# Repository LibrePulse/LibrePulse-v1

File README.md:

# PROJECT CURRENTLY IN THE MIDDLE OF SIGNIFICANT REDESIGN FROM THE INITIAL DRAFT

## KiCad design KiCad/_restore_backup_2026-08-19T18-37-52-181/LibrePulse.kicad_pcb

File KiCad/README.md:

# TODO:
## Cleanup
## Finish Schematic
## Start PCB

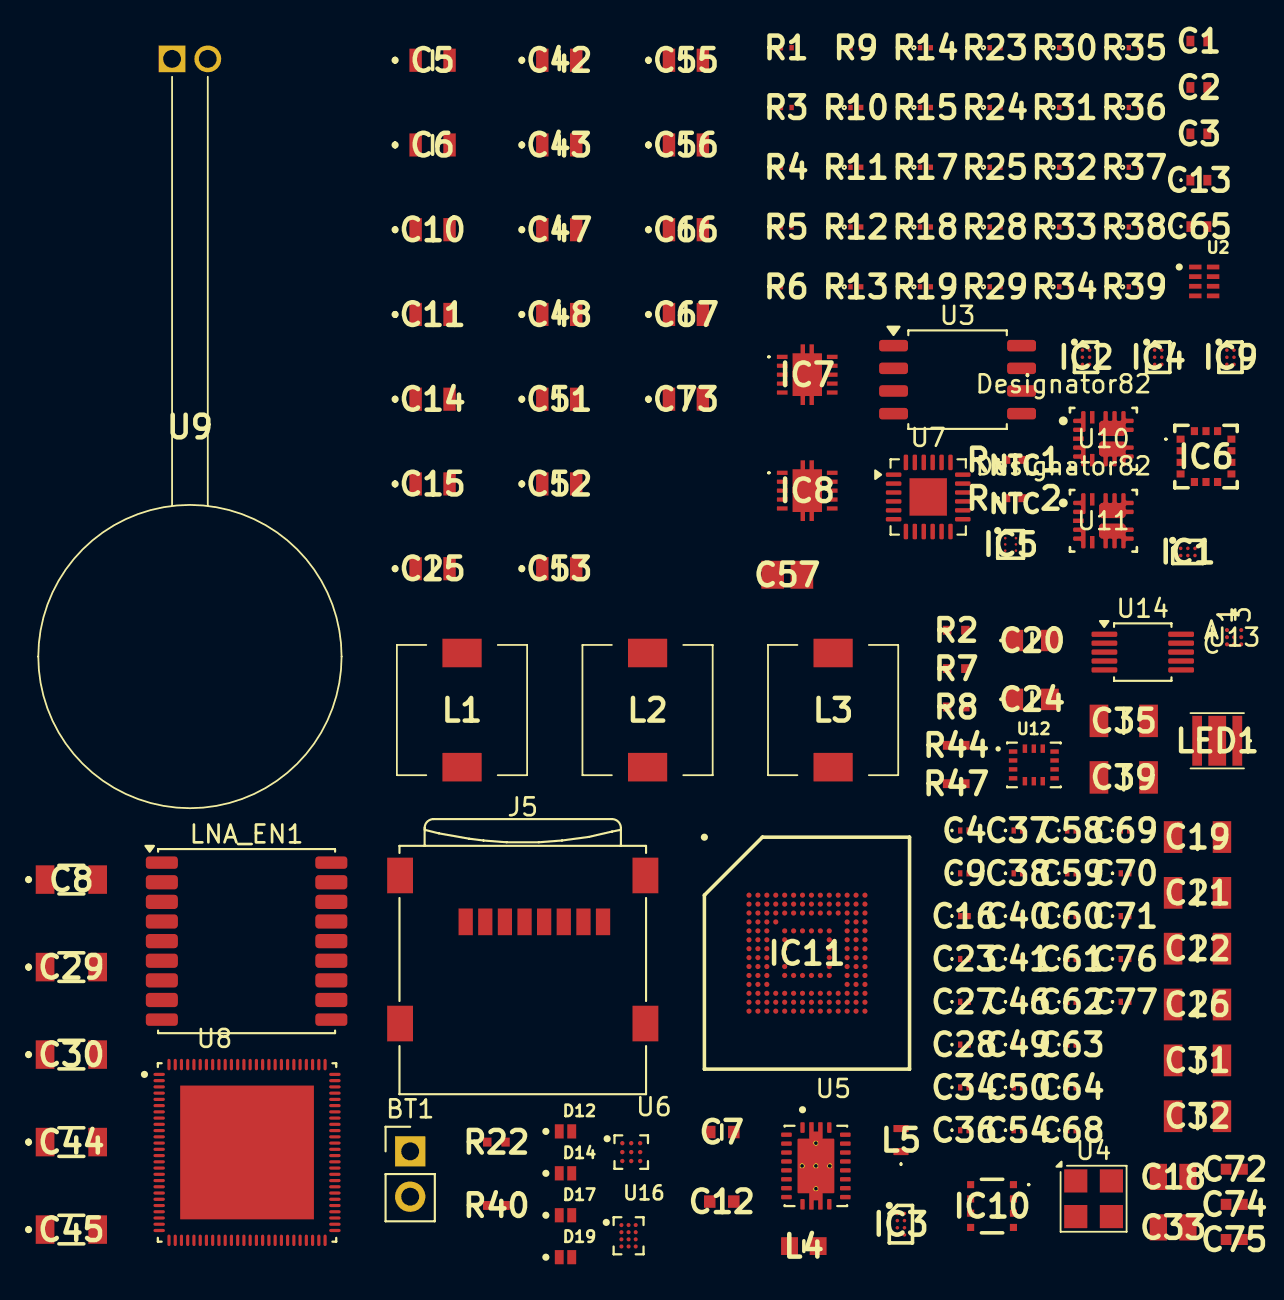
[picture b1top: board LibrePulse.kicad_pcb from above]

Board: 8 copper layers, 153 parts (0 on the bottom side), 104 nets, no tracks yet.

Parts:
BT1: DTP793435-1S1P-1300mAh-3.85V; PinHeader_1x02_P2.54mm_Vertical
C1, C2, C3, C13, C65: 1uF; GRM155R61H334ME01D
C4, C9, C16, C27, C28, C34, C36, C37, C38, C40, C41, C46, C49, C50, C54, C58, C59, C61, C62, C63, C64, C68, C69, C70, C71, C76, C77: 100nF; GRM033D70J224ME01D
C5, C10, C11, C15, C25, C42, C43, C47, C48, C51, C52, C55, C56, C66, C67, C73: 10uF; GRM21BR60J226ME39L
C6, C14, C53: 4.7uF; GRM21BR60J226ME39L
C7, C12: 2.2uF; GRM18x
C8, C29, C30, C44, C45: 22uF; GRM31x
C18, C33: 22nF; CAPC2012X145N
C19, C26: 10nF; CAPC3216X95N
C20, C24: 100nF; GRMJN65C1H104JE01D
C21, C22, C31, C32: 47nF; CAPC3216X95N
C23: 1nF; GRM033D70J224ME01D
C35, C39: 470nF; CAPC3216X180N
C57: 2.2uF; CAPC2212X200N
C60: 47pF; GRM033D70J224ME01D
C72, C74, C75: 47pF; CAPC1005X55N
D12, D14, D17, D19: PESD5V0V1BL; DIO_PESD5V5C1ULYL
IC1: AS6221; BGA6C40P3X2_149X102X60
IC2: TPS62841YBGR; BGA6C40P2X3_97X147X50
IC3: BQ21088YBGR; BGA8C40P2X4_100X155X50
IC4, IC9: TPS62840YBGR; BGA6C40P2X3_97X147X50
IC5: OPT3007YMFR; BGA6C35P2X3_86X95X23
IC6: ICU-10201; ICU10201
IC7, IC8: TPS7A9601DSCR
IC10: BME690
IC11: KLMCG4JETD-B041; BGA153C50P14X14_1150X1300X80
J5: Micro_SD_Card; microSD_HC_Wuerth_693072010801
L1, L2, L3: 2.2uH; 744777002
L4: 1uH; INDC1608X80N
L5: 0603DC-47NXJRW; 0603DC47NXJRW
LED1: KW_CSLPM1.TG-8N7P-EBVF46FCBB46; KWCSLNM1TG8M7NebvF46fcbB4615B5
LNA_EN1: MAX-M10S; ublox_MAX
R1, R3, R5, R6: 10K; ERJU01__0201_
R2, R7, R8: 47k; ERJ2RKD1004X
R4: 16k; ERJU01__0201_
R9, R10: 33; ERJU01__0201_
R11, R18, R19: 1M; ERJU01__0201_
R12, R17: 51k; ERJU01__0201_
R13: 196; ERJU01__0201_
R14: 10kΩ; ERJU01__0201_
R15, R33, R34: 10k; ERJU01__0201_
R22, R40: 10k; ERJS02_U02__0402_
R23, R24, R28, R29: 5.1k; ERJU01__0201_
R25: 1.5k; ERJU01__0201_
R30: 7.87k; ERJU01__0201_
R31: 11.5k; ERJU01__0201_
R32, R35: 30k; ERJU01__0201_
R36, R38: 12.7k; ERJU01__0201_
R37: 240k; ERJU01__0201_
R39: 90.9k; ERJU01__0201_
R44, R47: 4.7k; ERJ2RKD1004X
R_{NTC}1, R_{NTC}2: 10K; ERTJ0EA101H
U2: RV-3028-C8-32.768KHZ-1PPM-TA-QC
U3: W25Q128JVS; SOIC-8_5.3x5.3mm_P1.27mm
U4: MS5837-30BA; TE_MS5837-xxBA
U5: BQ51013CQWRHLRQ1; IC_BQ51013CQWRHLRQ1
U6: BQ27427YZFR
U7: PCAL6416AHF; HVQFN-24-1EP_4x4mm_P0.5mm_EP2.1x2.1mm
U8: ESP32-P4NRW32
U9: 760308101214
U10, U11: TPSM81299VCMR; VCM0007A-MFG
U12: BMI270
U13: BMM350
U14: DRV2605LDGS; TSSOP-10_3x3mm_P0.5mm
U16: LM3643YFFR; IC_LM3643YFFR

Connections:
+1V2: C5.1, C49.1, C55.1, IC2.A2 (VOS), L1.2, U8.26 (VDD_HP_0), U8.76 (VDD_HP_2), U8.91 (VDD_HP_3)
+1V8: C1.2, C2.2, C3.1, C34.1, C37.1, C45.1, C52.1, IC6.12 (VDD), IC6.13 (AVDD), IC8.8 (SNS), IC8.9 (OUT_1), IC8.10 (OUT_2), R39.2
+1V9: C11.1, C41.1, C43.1, C48.2, IC4.A2 (VOS), IC8.1 (IN_1), IC8.2 (IN_2), L2.2, R34.2, U8.9 (VDD_LP), U8.30 (VDD_FLASHIO), U8.59 (VDD_PSRAM_0), U8.67 (VDD_PSRAM_1), U8.71 (VDDO_FLASH), U8.72 (VDDO_PSRAM), U8.73 (VDDO_3), U8.74 (VDDO_4)
+2V5: C40.1, C42.1, C51.1, IC9.A2 (VOS), L3.2, U8.41 (VDD_MIPI_DPHY)
+3V3: C4.1, C27.1, C28.1, C30.1, C36.1, C38.1, C46.2, C50.1, C54.2, C56.1, C58.2, C59.1, C62.2, C63.2, C64.1, C66.1, C68.2, C69.2, C70.1, C71.2, C77.1, IC1.B1 (VDD), IC5.C1 (VDD), IC6.14 (VDDIO), IC10.2 (CSB), IC10.6 (VDDIO), IC10.8 (VDD), IC11.C6 (VDD_1), IC11.E6 (VDDF_1), IC11.F5 (VDDF_2), IC11.J10 (VDDF_3), IC11.K9 (VDDF_4), IC11.M4 (VDD_2), IC11.N4 (VDD_3), IC11.P3 (VDD_4), IC11.P5 (VDD_5), J5.4 (VDD), L4.2, LNA_EN1.6 (V_BCKP), LNA_EN1.7 (VCC_IO), LNA_EN1.8 (VCC), R1.2, R2.2, R3.2, R5.2, R14.2, R22.2, R44.2, R47.2, U2.7 (VDD), U3.8 (VCC), U4.2 (VDD), U7.21 (V_{DD(P)}), U7.23 (V_{DD(I2C-bus)}), U8.21 (VDD_IO_0), U8.51 (VDD_USBPHY), U8.62 (VDD_IO_4), U8.75 (VDD_LDO), U8.77 (VDD_DCDCC), U8.85 (VDD_IO_5), U8.96 (VDD_IO_6), U8.101 (VDD_ANA), U8.102 (VDD_BAT), U11.2 (VOUT), U12.2 (ASDX), U12.3 (ASCX), U12.5 (VDDIO), U12.8 (VDD), U12.12 (CSB), U13.B3 (VDDIO), U13.C1 (VDD), U14.6 (VDD/NC), U14.10 (VDD), U16.A2 (IN)
+4V5: C44.1, IC7.9 (OUT_1), IC7.10 (OUT_2), R37.2
+5V0: C29.1, C47.2, IC7.1 (IN_1), IC7.2 (IN_2), R33.2, U10.2 (VOUT)
+VSYS: BT1.1 (+), C8.1, C12.2, C13.1, IC3.B2 (SYS), IC3.C2 (BAT), R15.2, R18.2, R19.2, U6.B2 (VSS), U6.C1 (VSS), U6.C2 (SRX), U6.C3 (BAT), U10.4 (AVIN), U10.5 (PVIN), U11.4 (AVIN), U11.5 (PVIN)
/AS6221_A2: IC1.A2 (ALERT/ADD1), U8.14 (GPIO13)
/AS6221_B2: IC1.B2 (ADD0), U8.15 (GPIO14)
/BMI270_INT1: U7.2 (P0_1), U12.4 (INT1)
/BMI270_INT2: U7.3 (P0_2), U12.9 (INT2)
/BMM350_INT: U7.4 (P0_3), U13.A1 (INT)
/CLKOUT: U2.1 (CLKOUT), U8.100 (XTAL_P)
/EN_PWR: U8.25 (GPIO23), U10.7 (EN), U11.7 (EN)
/IC1_C1: IC2.C1 (EN), IC4.C1 (EN), IC9.C1 (EN)
/INT: LNA_EN1.4 (TIMEPULSE), U8.88 (GPIO46)
/INT_PWR: IC3.A1 (~INT), R5.1
/MAX-M10S_LNA_EN: LNA_EN1.13 (LNA_EN), U8.64 (GPIO33)
/PCAL6416A_VDD_I2C-BUS: R22.1, U7.24 (~RESET)
/RSTN: IC11.K5 (RSTN), U8.86 (GPIO44)
/RV-3028-C8-INT: U2.2 (~INT), U7.1 (P0_0)
/RXD: LNA_EN1.3 (RXD), U8.84 (GPIO43)
/SCL: IC1.A3 (SCL), IC3.B1 (SCL), IC5.A2 (SCL), IC10.4 (SCK), R1.1, R44.1, U2.3 (SCL), U4.3 (SCL), U7.19 (SCL), U8.53 (GPIO25), U12.13 (SCX), U13.A3 (SCK), U14.2 (SCL), U16.B3 (SCL)
/SDA: IC1.B3 (SDA), IC3.C1 (SDA), IC5.C2 (SDA), IC10.3 (SDI), R3.1, R47.1, U2.4 (SDA), U4.4 (SDA), U7.20 (SDA), U8.55 (GPIO26), U12.14 (SDX), U13.A2 (SDA), U14.3 (SDA), U16.A3 (SDA)
/SDMMC_CLK: IC11.M6 (CLK), U8.3 (GPIO3)
/SDMMC_CMD: IC11.M5 (CMD), U8.4 (GPIO4)
/SDMMC_D0: IC11.A3 (DAT0), U8.13 (GPIO12)
/SDMMC_D1: IC11.A4 (DAT1), U8.92 (GPIO49)
/SDMMC_D2: IC11.A5 (DAT2), U8.93 (GPIO50)
/SDMMC_D3: IC11.B2 (DAT3), U8.94 (GPIO51)
/SDMMC_D4: IC11.B3 (DAT4), U8.95 (GPIO52)
/SDMMC_D5: IC11.B4 (DAT5), U8.97 (GPIO53)
/SDMMC_D6: IC11.B5 (DAT6), U8.89 (GPIO47)
/SDMMC_D7: IC11.B6 (DAT7), U8.90 (GPIO48)
/SD_CLK: J5.5 (CLK), U8.24 (GPIO22)
/SD_DAT0: J5.7 (DAT0), U8.20 (GPIO19)
/SD_DAT2: J5.1 (DAT2), U8.22 (GPIO20)
/SD_DAT3: J5.2 (DAT3/CD), U8.23 (GPIO21)
/SPI.CS: IC6.5 (CS_B), U8.17 (GPIO16)
/SPI.MOSI: IC6.3 (MOSI), U8.18 (GPIO17)
/SPI.SCK: IC6.2 (SCLK), U8.19 (GPIO18), U8.87 (GPIO45)
/SYS: C6.1, C14.1, IC2.B1 (VIN), IC4.B1 (VIN)
/TXD: LNA_EN1.2 (TXD), U8.83 (GPIO42)
/U6_2: C18.1, C19.1, C20.1, C23.2, U5.2 (AC1)
/U6_3: C19.2, U5.3 (BOOT1)
/U6_5: C39.2, U5.5 (CLAMP1)
/U6_6: C18.2, U5.6 (COMM1)
/U6_14: C23.1, C26.1, C33.1, C35.1, C39.1, U5.19 (AC2), U9.2
/U6_15: C33.2, U5.15 (COMM2)
/U6_16: C35.2, U5.16 (CLAMP2)
/U6_17: C26.2, U5.17 (BOOT2)
/U16_B2: U8.6 (GPIO6), U16.B2 (STROBE)
/U16_C2: U8.1 (GPIO1), U16.C2 (HWEN)
/U16_C3: U8.5 (GPIO5), U16.C3 (TORCH/TEMP)
/V_WIRELESS: C7.1, C24.1, C25.1, IC3.A2 (IN), U5.4 (OUT)
GND: BT1.2 (-), C1.1, C2.1, C3.2, C4.2, C5.2, C6.2, C7.2, C8.2, C9.1, C10.1, C11.2, C13.2, C14.2, C15.1, C16.2, C24.2, C25.2, C27.2, C28.2, C29.2, C30.2, C34.2, C36.2, C37.2, C38.2, C40.2, C41.2, C42.2, C43.2, C44.2, C45.2, C46.1, C47.1, C48.1, C49.2, C50.2, C51.2, C52.2, C53.2, C54.1, C55.2, C56.2, C57.2, C58.1, C59.2, C60.2, C61.1, C61.2, C62.1, C63.1, C64.2, C65.1, C66.2, C67.2, C68.1, C69.1, C70.2, C71.1, C72.2, C73.2, C74.2, C75.2, C76.2, C77.2, IC1.A1 (VSS), IC2.A1 (GND), IC3.D2 (GND), IC4.A1 (GND), IC4.C2 (VSET), IC5.A1 (GND), IC6.1 (GND_1), IC6.8 (GND_2), IC6.11 (GND_3), IC7.6 (GND), IC8.6 (GND), IC9.A1 (GND), IC10.1 (GND_1), IC10.5 (SDO), IC10.7 (GND_2), IC11.A6 (VSS_1), IC11.C4 (VSS_2), IC11.E7 (VSS_3), IC11.G5 (VSS_4), IC11.H10 (VSS_5), IC11.J5 (VSS_6), IC11.K8 (VSS_7), IC11.N2 (VSS_8), IC11.N5 (VSS_9), IC11.P4 (VSS_10), IC11.P6 (VSS_11), J5.6 (VSS), J5.SH (SHIELD), LED1.3 (NO_CONTACT_PAD), LNA_EN1.1 (GND), LNA_EN1.10 (GND), LNA_EN1.12 (GND), R4.2, R6.2, R7.2, R8.2, R9.1, R10.2, R13.2, R30.2, R31.2, R32.2, R35.2, R36.1, R38.1, R40.2, R_{NTC}1.2, R_{NTC}2.2, U2.5 (VSS), U3.4 (GND), U4.1 (GND), U5.1 (PGND), U5.9 (AD), U5.12 (ILIM), U5.20 (PGND), U5.21 (EXP), U7.9 (V_{SS}), U7.25 (EP), U8.105 (GND), U10.3 (GND), U11.1 (VSEL), U11.3 (GND), U12.1 (SDO), U12.6 (GNDIO), U12.7 (GND), U13.B1 (GND), U13.B2 (ADSEL), U13.C3 (BYPASS), U14.4 (IN/TRIG), U14.8 (GND), U16.A1 (GND), U16.D2 (TX)
unnamed: C20.2, U9.1
unnamed: C21.1, R23.1
unnamed: C22.1, R24.1
unnamed: C31.1, R28.1
unnamed: C32.1, R29.1
unnamed: R12.2, R24.2
unnamed: R17.2, R29.2
unnamed: IC2.B2 (SW), L1.1
unnamed: IC2.C2 (VSET), R4.1
unnamed: IC3.D1 (TS/MR), R6.1
unnamed: IC4.B2 (SW), L2.1
unnamed: IC7.5 (FB_PG), R36.2, R37.1
unnamed: IC7.7 (NR/SS), R32.1
unnamed: IC7.4 (PG), R33.1
unnamed: IC8.5 (FB_PG), R38.2, R39.1
unnamed: IC8.7 (NR/SS), R35.1
unnamed: IC8.4 (PG), R34.1
unnamed: IC9.B2 (SW), L3.1
unnamed: C53.1, IC9.B1 (VIN)
unnamed: IC9.C2 (VSET), R31.1
unnamed: C65.2, IC11.C2 (VDDI)
unnamed: C67.1, LED1.2 (A), U16.C1 (OUT)
unnamed: LED1.1 (K), U16.D3 (LED1)
unnamed: C72.1, L5.1, LNA_EN1.11 (RF_IN)
unnamed: C73.1, C74.1, C75.1, L5.2, LNA_EN1.14 (VCC_RF)
unnamed: R9.2, R10.1
unnamed: R11.1, R12.1
unnamed: U3.6 (CLK), U8.32 (FLASH_CK)
unnamed: U3.5 (DI/IO_{0}), U8.28 (FLASH_Q)
unnamed: U3.2 (DO/IO_{1}), U8.33 (FLASH_D)
unnamed: U3.1 (~CS), U8.27 (FLASH_CS)
unnamed: U3.7 (~HOLD/~RESET/IO_{3}), U8.31 (FLASH_HOLD)
unnamed: U3.3 (~WP/IO_{2}), U8.29 (FLASH_WP)
unnamed: R13.1, U5.14 (FOD)
unnamed: C9.2, C10.2, C15.2, U5.18 (RECT)
unnamed: R25.1, R_{NTC}2.1, U5.13 (TS/CTRL)
unnamed: R_{NTC}1.1, U6.B1 (BIN)
unnamed: R15.1, U6.A1 (GPOUT)
unnamed: R18.1, U6.A3 (SCL)
unnamed: R19.1, U6.A2 (SDA)
unnamed: C12.1, U6.B3 (VDD)
unnamed: C16.1, R14.1, U8.103 (CHIP_PU)
unnamed: R30.1, U10.1 (VSEL)
unnamed: C57.1, U13.C2 (CRST)
unnamed: R40.1, U14.5 (EN)
unnamed: C60.1, U14.1 (REG)
unnamed: L4.1, U16.B1 (SW)
